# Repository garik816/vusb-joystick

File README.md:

# vusb-joystick
atmega328p, v-usb, EasyHID

потерялся приёмник freedom cordless joystick 2.4

"привязал" за провод)

за основу взял библеотеку Гайвера EasyHID

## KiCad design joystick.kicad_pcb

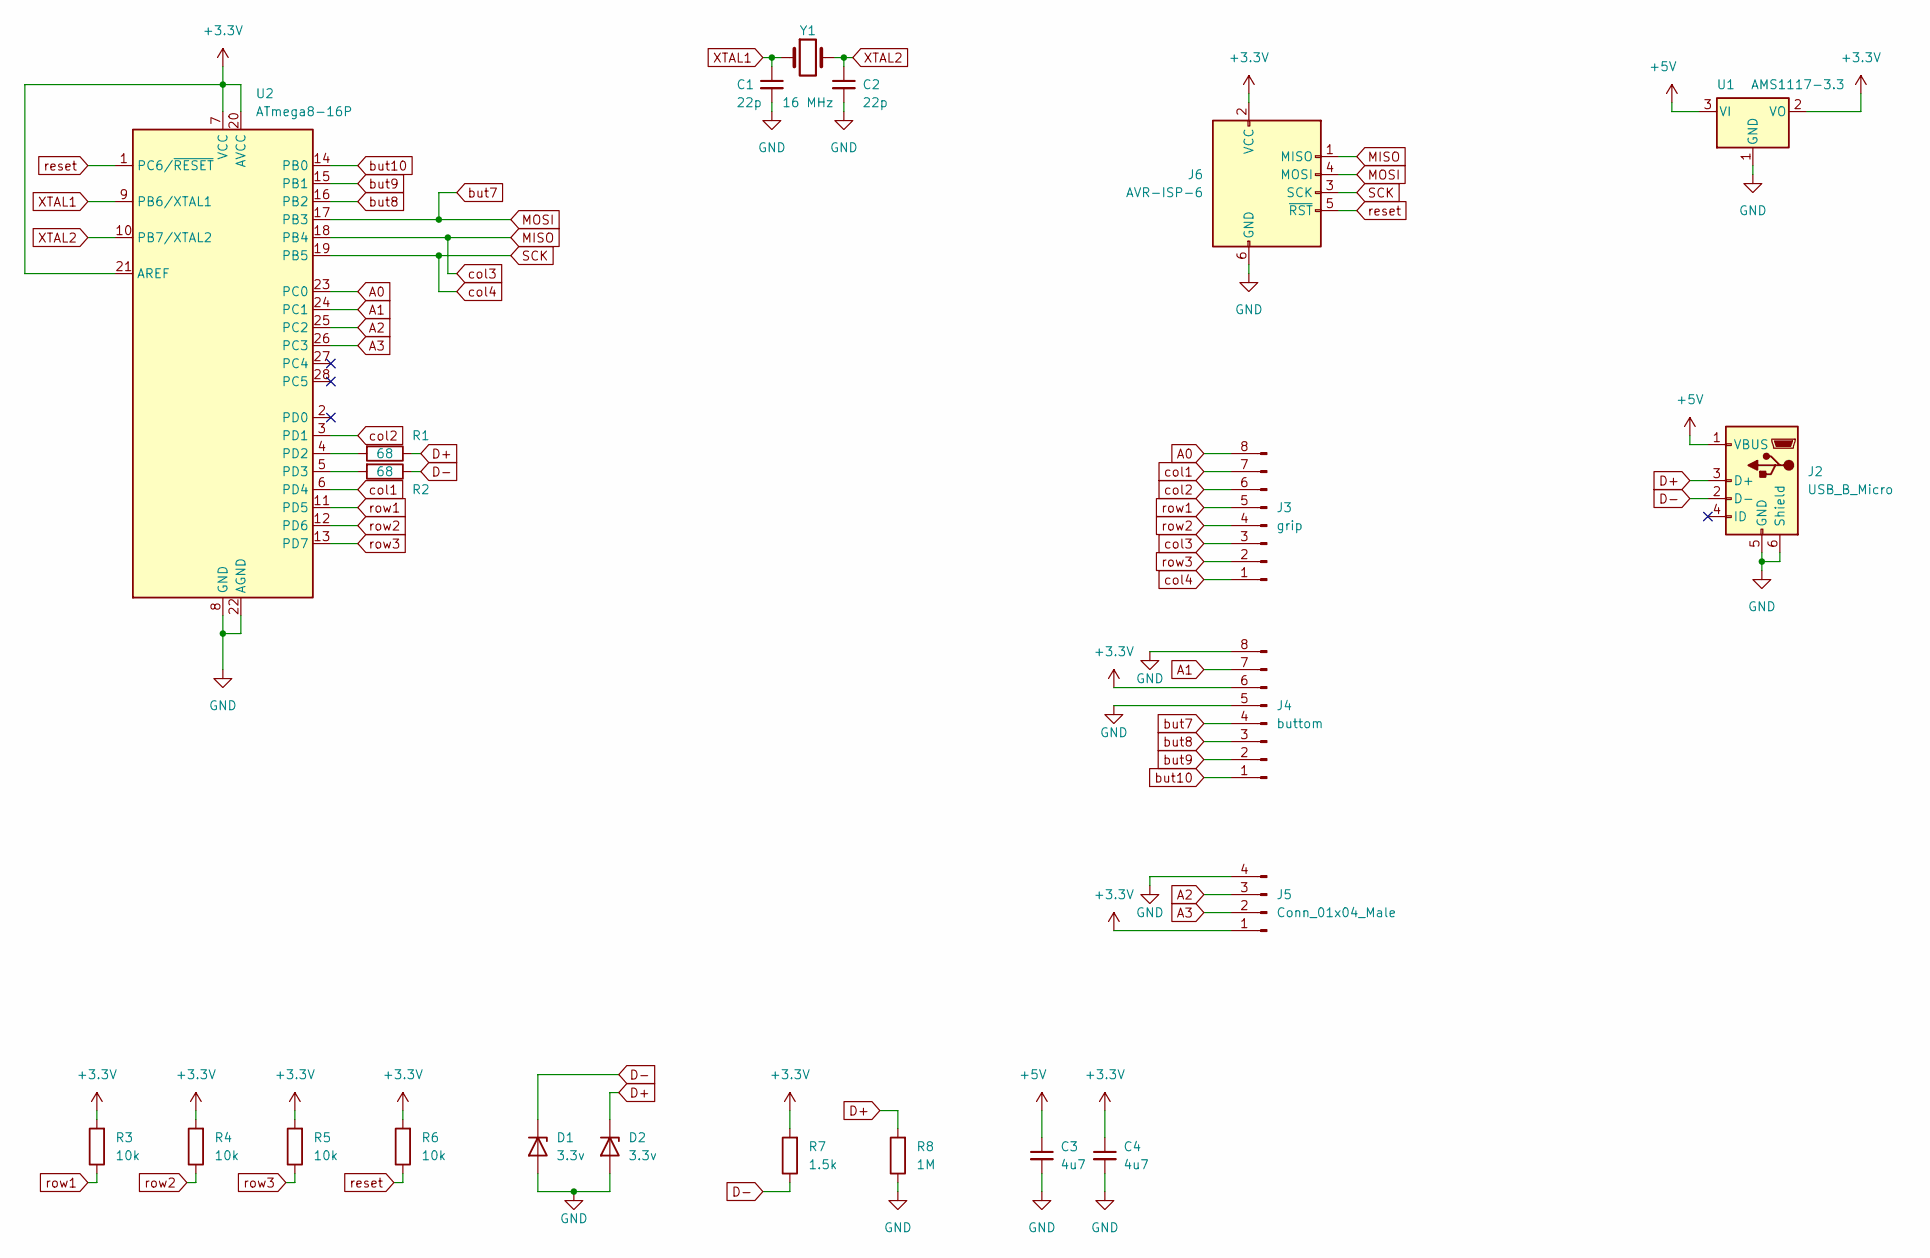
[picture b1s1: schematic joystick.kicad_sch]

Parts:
C1, C2: 22p; C_0805_2012Metric
C3, C4: 4u7; CP_Radial_D4.0mm_P1.50mm
D1, D2: 3.3v; D_1206_3216Metric
J2: USB_B_Micro; USB_Micro-B_Amphenol_10103594-0001LF_Horizontal
J3: grip; PinHeader_1x08_P2.00mm_Vertical
J4: buttom; PinHeader_1x08_P2.00mm_Vertical
J5: Conn_01x04_Male; PinHeader_1x04_P2.00mm_Vertical
J6: AVR-ISP-6; IDC-Header_2x03_P2.54mm_Vertical
R1, R2: 68; R_0805_2012Metric
R3, R4, R5, R6: 10k; R_0805_2012Metric
R7: 1.5k; R_0805_2012Metric
R8: 1M; R_0805_2012Metric
U1: AMS1117-3.3; SOT-223-3_TabPin2
U2: ATmega8-16P; DIP-28_W7.62mm
Y1: 16 MHz; Crystal_HC50_Vertical

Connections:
+3.3V: C4.1, J4.6, J5.1, J6.2 (VCC), R3.2, R4.2, R5.2, R6.2, R7.2, U1.2 (VO), U2.7 (VCC), U2.20 (AVCC), U2.21 (AREF)
+5V: C3.1, J2.1 (VBUS), U1.3 (VI)
A0: J3.8, U2.23 (PC0)
A1: J4.7, U2.24 (PC1)
A2: J5.3, U2.25 (PC2)
A3: J5.2, U2.26 (PC3)
D+: D2.1 (K), J2.3 (D+), R1.1, R8.2
D-: D1.1 (K), J2.2 (D-), R2.1, R7.1
GND: C1.2, C2.2, C3.2, C4.2, D1.2 (A), D2.2 (A), J2.5 (GND), J2.6 (Shield), J4.5, J4.8, J5.4, J6.6 (GND), R8.1, U1.1 (GND), U2.8 (GND), U2.22 (AGND)
MISO: J3.3, J6.1 (MISO), U2.18 (PB4)
MOSI: J4.4, J6.4 (MOSI), U2.17 (PB3)
unnamed: R1.2, U2.4 (PD2)
unnamed: R2.2, U2.5 (PD3)
SCK: J3.1, J6.3 (SCK), U2.19 (PB5)
XTAL1: C1.1, U2.9 (PB6/XTAL1), Y1.1
XTAL2: C2.1, U2.10 (PB7/XTAL2), Y1.2
but8: J4.3, U2.16 (PB2)
but9: J4.2, U2.15 (PB1)
but10: J4.1, U2.14 (PB0)
col1: J3.7, U2.6 (PD4)
col2: J3.6, U2.3 (PD1)
reset: J6.5 (~RST), R6.1, U2.1 (PC6/~RESET)
row1: J3.5, R3.1, U2.11 (PD5)
row2: J3.4, R4.1, U2.12 (PD6)
row3: J3.2, R5.1, U2.13 (PD7)

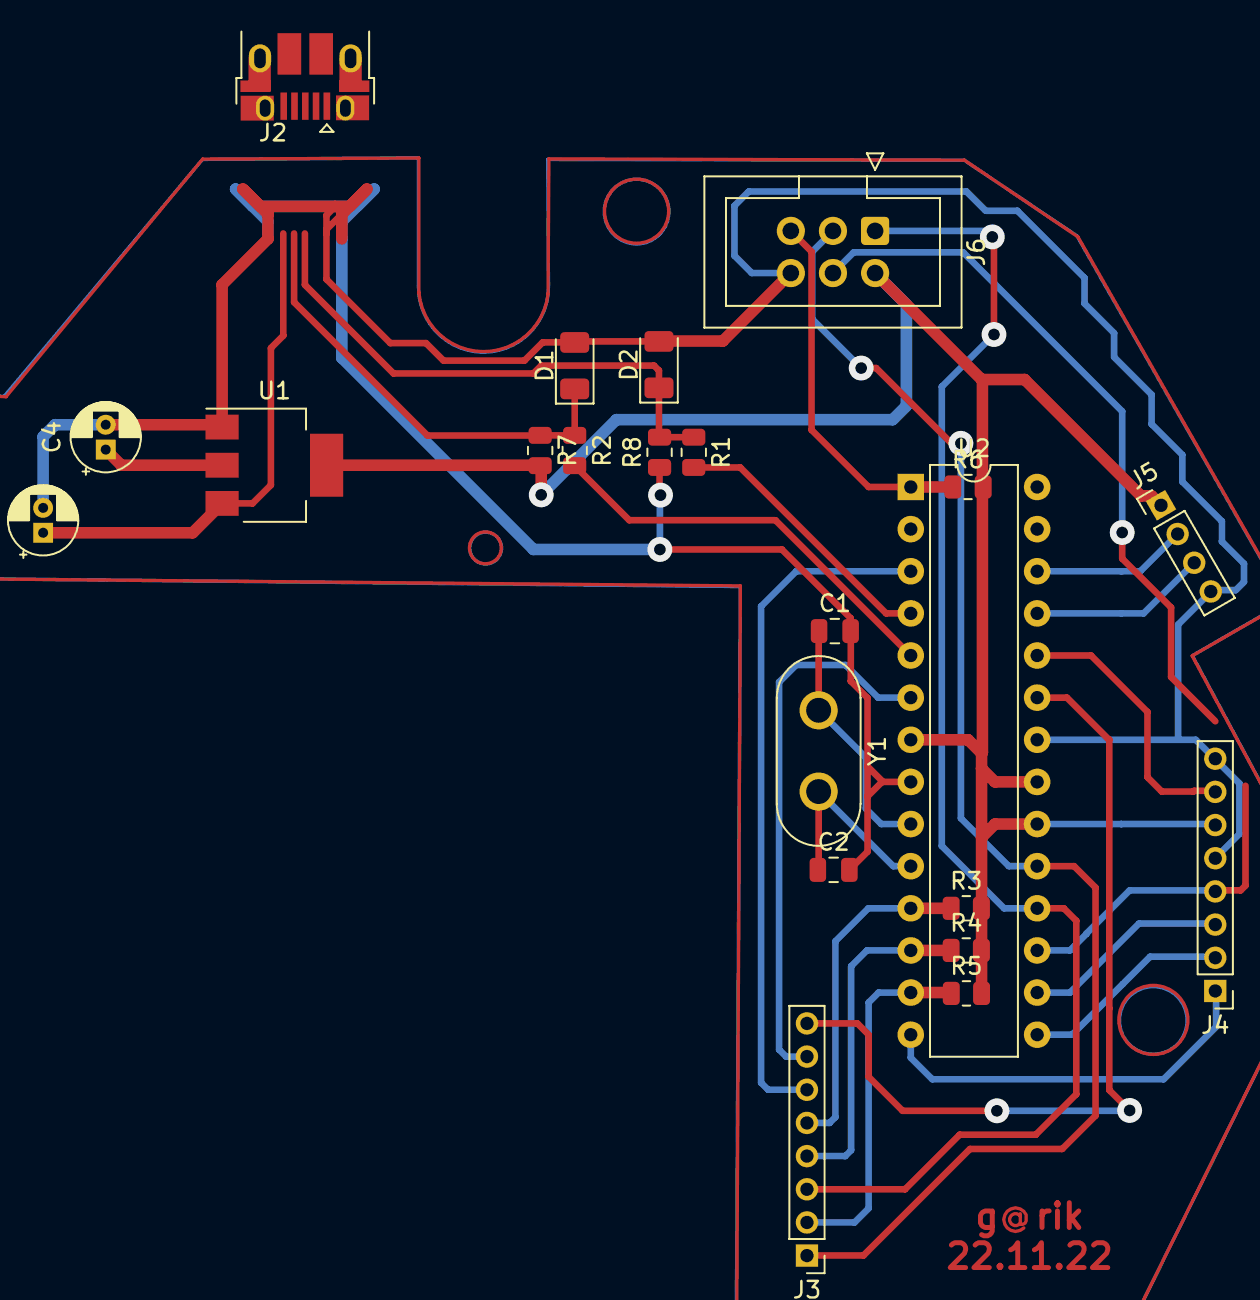
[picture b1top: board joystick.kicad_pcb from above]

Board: 2 copper layers, 22 parts (0 on the bottom side), 25 nets.

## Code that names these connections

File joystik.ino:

//////////////////////////////////////////
// ручка
// PC0  - 14/A0     - поворот ручки
// PD4  - 4   - col1  - 1-я строка
// PD1  - 1   - col2  - 2-я строка
// PD5  - 5   - row1  - 1-й столбец
// PD6  - 6   - row2  - 2-й столбец
// PB4  - 12  - col3  - 3-я строка (z_neg)
// PD7  - 7   - row3  - 3-й столбец
// PB5  - 13  - col4  - 4-я строка (z_pos)

// кнопки
// GND
// PC1  - 15/A1    - газ 
// VCC
// GND
// PB3  - 11  - but7  - общий gnd
// PB2  - 10  - but8  - общий gnd
// PB1  - 9   - but9  - общий gnd
// PB0  - 8   - but10 - общий gnd

// оси
// VCC
// PC2  - 16/A2    - ось Y
// PC3  - 17/A3    - ось X
// GND

// USB
// PD2  - 2 - D+
// PD3  - 3 - D-

// blinker
// PC5  - 19/A5  - общий gnd
//////////////////////////////////////////

#include <EasyHID.h>


const char k4x3 [4][3] = {      // символы на клавиатуре
  {'2', 'r', '-'},
  {'4', 'l', '5'},
  {'6', 'd', '1'},
  {'3', 'u', '-'}
};

#define LED_PIN 19

#define axis_z_PIN A0
#define axis_acceleration A1
#define axis_x_PIN A2
#define axis_y_PIN A3

#define but10 8
#define but9 9
#define but8 10
#define but7 11

#define D_pos 2
#define D_neg 3

const int P[] = {4, 1, 12, 13}; // пины строк
const int M[] = {5, 6, 7};   // пины столбцов

#define Ry_pos 13
#define Ry_neg 12

long axisX = 0;
long axisY = 0;
long axisZ = 0;
long axisT = 0;

static unsigned long timer = millis();

uint8_t report_buffer[8];

void setup() {
  // Serial.begin(9600);
  analogReference(DEFAULT);
  HID.begin();
  pinMode (LED_PIN, OUTPUT);
  init_joy();
}

void loop() {
  blink();
  clearReport();
  read_joy();
  // test();
  // HID.tick();
  usbReportSend(7);
}

void blink(void){
  if (millis() - timer > 1000) {
    timer = millis();
    digitalWrite(LED_PIN, !digitalRead(LED_PIN));
  }
}

void test(void){
  report_buffer [0] = 0xff;
	report_buffer [1] = 0xee;
	report_buffer [2] = 0xdd;
	report_buffer [3] = 0xcc;
	report_buffer [4] = 0xbb;
	report_buffer [5] = 0xaa;
  report_buffer [6] = 0x88;
  report_buffer [7] = 0x77;
}

int averageAnalogread(int analogInPin, int samples){
   unsigned int avg_sum=0;
   for(byte i=0;i<samples;i++){
       avg_sum+=analogRead(analogInPin);
       delay(2); // небольшая пауза между замерами
   }
    
   return avg_sum/samples;
}
	

void detectAxisXYZ(void){

  // int sensX = analogRead(A2);
  // int sensY = analogRead(A3);
  // int sensRx = analogRead(A1);

  int sensX = averageAnalogread(A2,7);
  int sensY = averageAnalogread(A3,7);
  int sensRx = averageAnalogread(A1,7);




  int reportValueX = map(sensX, 0, 1023, 0, 255)+127;
  int reportValueY = map(sensY, 0, 1023, 0, 255)+127;
  int reportValueRx = map(sensRx, 0, 1023, 255, 0)+127;

  report_buffer[0] = reportValueX;
  report_buffer[1] = reportValueY;
  report_buffer[2] = reportValueRx;
}

void detectAxisRy(void){
  pinMode(Ry_pos, OUTPUT);
  pinMode(Ry_neg, OUTPUT);
  digitalWrite(Ry_pos, HIGH);
  digitalWrite(Ry_neg, LOW);
  delay(10);

  // int sensRy = analogRead(A0);
  int sensRy = averageAnalogread(A0,10);
  int reportValueRy = map(sensRy, 0, 1023, 0, 255)-127; // преобразуем в диапазон 0-255
  report_buffer[3] = reportValueRy; // записываем значение в элемент массива report для оси Z
}

static void init_joy( void )
{
  for (int i = 0; i <= 3; i++) {  // выставляем пины строк на выход, столбцов на вход
    pinMode(P[i], OUTPUT);
    digitalWrite(P[i], HIGH);
  }
  for (int i = 0; i <= 2; i++) {
    pinMode(M[i], INPUT_PULLUP);
  }

  pinMode (but7, INPUT_PULLUP);
  pinMode (but8, INPUT_PULLUP);
  pinMode (but9, INPUT_PULLUP);
  pinMode (but10, INPUT_PULLUP);
}

void clearReport(void){
  report_buffer [0] = 0;
	report_buffer [1] = 0;
	report_buffer [2] = 0;
	report_buffer [3] = 0;
	report_buffer [4] = 0;
	report_buffer [5] = 0;
  report_buffer [6] = 0;
  report_buffer [7] = 0;
}

void read_joy( void )
{

  detectAxisXYZ();
  detectAxisRy();

	// Buttons
	if (getGripKey()=='1') report_buffer[4] |= 0x01;		        //PRESSED  1
	if (getGripKey()=='2') report_buffer[4] |= 0x02;    		    //PRESSED  2
	if (getGripKey()=='3') report_buffer[4] |= 0x04;		        //PRESSED  3
	if (getGripKey()=='4') report_buffer[4] |= 0x08;		        //PRESSED  4
	if (getGripKey()=='5') report_buffer[4] |= 0x10;		        //PRESSED  5
	if (getGripKey()=='6') report_buffer[4] |= 0x20;		        //PRESSED  6
	if (!digitalRead(but7)) report_buffer[4] |= 0x80;	     		  //PRESSED  7
	if (!digitalRead(but8)) report_buffer[4] |= 0x40;			      //PRESSED  8
	if (!digitalRead(but9)) report_buffer[5] |= 0x01;			      //PRESSED  9
	if (!digitalRead(but10)) report_buffer[5] |= 0x02;			    //PRESSED  10

  // d-pad
  if (getGripKey()=='u') report_buffer[6] |= 0x01;
  if (getGripKey()=='d') report_buffer[6] |= 0x02;
  if (getGripKey()=='l') report_buffer[6] |= 0x04;
  if (getGripKey()=='r') report_buffer[6] |= 0x08;
}

char getGripKey() {
  static unsigned long timer;
  char a = 0;
  for (byte p = 0; p <= 3; p++) {    // последовательно выставляем по одной строке в LOW
    digitalWrite(P[p], LOW);
    for (byte m = 0; m <= 2; m++) {  // и считываем столбцы вылавнивая где LOW происходит
      if (!digitalRead(M[m])) {
        a = k4x3[p][m];             // считываем соотвествующий символ для комбинации столбца и строки
      }
    }
    digitalWrite(P[p], HIGH);       // возвращем строку в HIGH и крутим дальше
  }
  timer = millis();
  return a;
}

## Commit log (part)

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2023-09-13 Create asd
2023-09-13 Rename joystick.kicad_pro to Kicad6/joystick.kicad_pro
